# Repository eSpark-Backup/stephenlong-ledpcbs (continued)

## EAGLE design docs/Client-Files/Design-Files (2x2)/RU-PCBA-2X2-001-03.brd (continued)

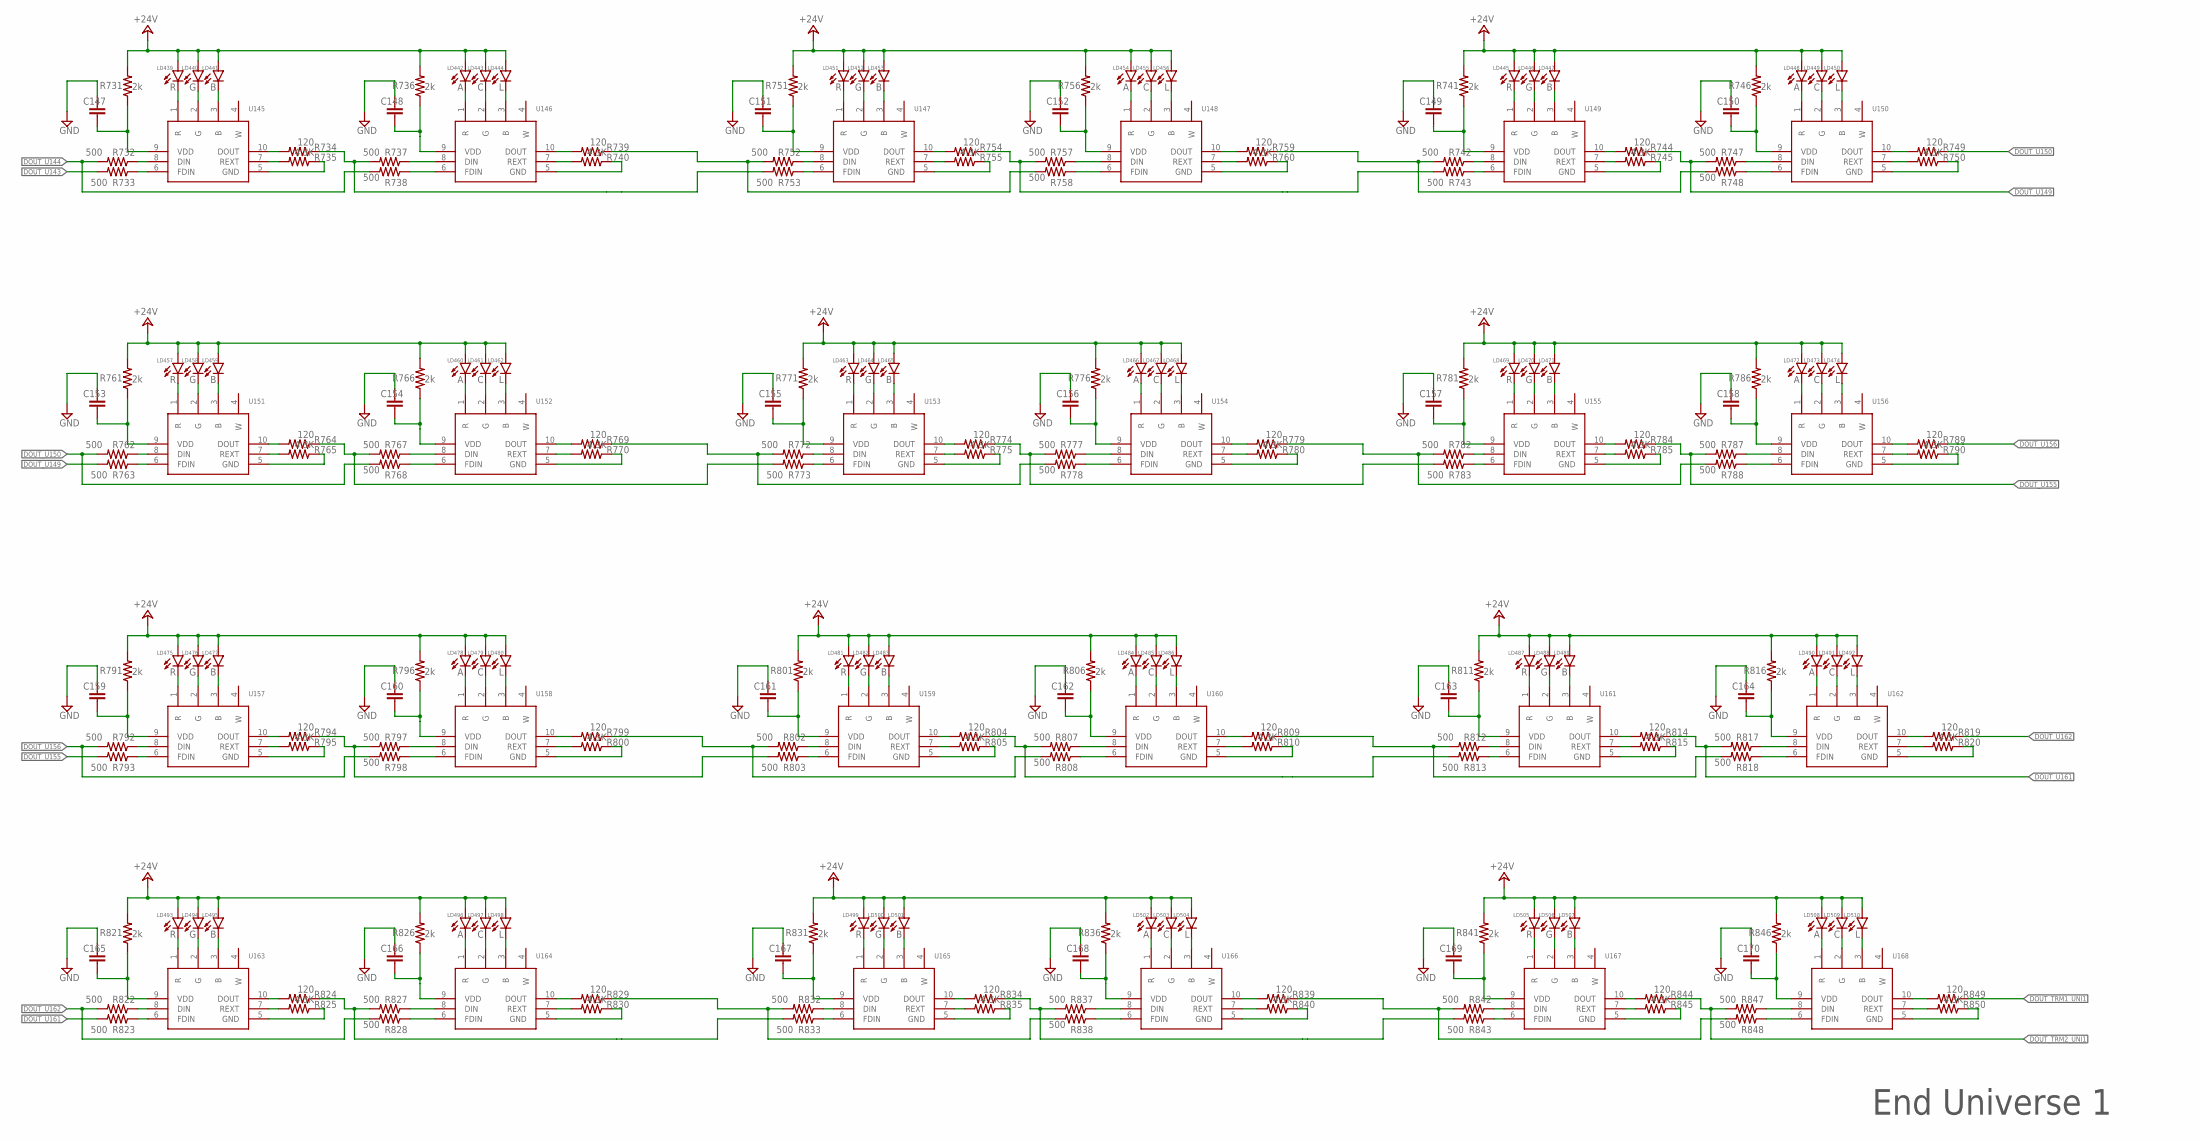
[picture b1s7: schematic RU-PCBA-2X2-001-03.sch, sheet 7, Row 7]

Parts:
C147, C148, C149, C150, C151, C152, C153, C154, C155, C156, C157, C158, C159, C160, C161, C162, C163, C164, C165, C166, C167, C168, C169, C170: C-EUC1206; C1206; MPN C_104
LD439, LD445, LD451, LD457, LD463, LD469, LD475, LD481, LD487, LD493, LD499, LD505: R; 5050LED; MPN R_5050
LD440, LD446, LD452, LD458, LD464, LD470, LD476, LD482, LD488, LD494, LD500, LD506: G; 5050LED; MPN G_5050
LD441, LD447, LD453, LD459, LD465, LD471, LD477, LD483, LD489, LD495, LD501, LD507: B; 5050LED; MPN B_5050
LD442, LD448, LD454, LD460, LD466, LD472, LD478, LD484, LD490, LD496, LD502, LD508: A; 5050LED; MPN A_5050
LD443, LD449, LD455, LD461, LD467, LD473, LD479, LD485, LD491, LD497, LD503, LD509: C; 5050LED; MPN C_5050
LD444, LD450, LD456, LD462, LD468, LD474, LD480, LD486, LD492, LD498, LD504, LD510: L; 5050LED; MPN L_5050
R731, R736, R741, R746, R751, R756, R761, R766, R771, R776, R781, R786, R791, R796, R801, R806, R811, R816, R821, R826, R831, R836, R841, R846: 2k; R1206; MPN R_VDD
R732, R733, R737, R738, R742, R743, R747, R748, R752, R753, R757, R758, R762, R763, R767, R768, R772, R773, R777, R778, R782, R783, R787, R788, R792, R793, R797, R798, R802, R803, R807, R808, R812, R813, R817, R818, R822, R823, R827, R828, R832, R833, R837, R838, R842, R843, R847, R848: 500; R0805; MPN R_500
R734, R739, R744, R749, R754, R759, R764, R769, R774, R779, R784, R789, R794, R799, R804, R809, R814, R819, R824, R829, R834, R839, R844, R849: 120; R0805; MPN R_120
R735, R740, R745, R750, R755, R760, R765, R770, R775, R780, R785, R790, R795, R800, R805, R810, R815, R820, R825, R830, R835, R840, R845, R850: 4.3K; R0805; MPN R_EXT
U145, U146, U147, U148, U149, U150, U151, U152, U153, U154, U155, U156, U157, U158, U159, U160, U161, U162, U163, U164, U165, U166, U167, U168: UCS7604; SOP100P600X175-10N; MPN UCS7604

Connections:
+24V: LD439.A, LD440.A, LD441.A, LD442.A, LD443.A, LD444.A, LD445.A, LD446.A, LD447.A, LD448.A, LD449.A, LD450.A, LD451.A, LD452.A, LD453.A, LD454.A, LD455.A, LD456.A, LD457.A, LD458.A, LD459.A, LD460.A, LD461.A, LD462.A, LD463.A, LD464.A, LD465.A, LD466.A, LD467.A, LD468.A, LD469.A, LD470.A, LD471.A, LD472.A, LD473.A, LD474.A, LD475.A, LD476.A, LD477.A, LD478.A, LD479.A, LD480.A, LD481.A, LD482.A, LD483.A, LD484.A, LD485.A, LD486.A, LD487.A, LD488.A, LD489.A, LD490.A, LD491.A, LD492.A, LD493.A, LD494.A, LD495.A, LD496.A, LD497.A, LD498.A, LD499.A, LD500.A, LD501.A, LD502.A, LD503.A, LD504.A, LD505.A, LD506.A, LD507.A, LD508.A, LD509.A, LD510.A, R731.2, R736.2, R741.2, R746.2, R751.2, R756.2, R761.2, R766.2, R771.2, R776.2, R781.2, R786.2, R791.2, R796.2, R801.2, R806.2, R811.2, R816.2, R821.2, R826.2, R831.2, R836.2, R841.2, R846.2; also elsewhere on the board
DOUT_TRM1_UNI1: R849.1
DOUT_TRM2_UNI1: R844.1, R847.2
DOUT_U143: R733.2; also elsewhere on the board
DOUT_U144: R732.2, R738.2; also elsewhere on the board
DOUT_U149: R744.1, R747.2, R763.2
DOUT_U150: R749.1, R762.2, R768.2
DOUT_U155: R784.1, R787.2, R793.2
DOUT_U156: R789.1, R792.2, R798.2
DOUT_U161: R814.1, R817.2, R823.2
DOUT_U162: R819.1, R822.2, R828.2
GND: C147.2, C148.2, C149.2, C150.2, C151.2, C152.2, C153.2, C154.2, C155.2, C156.2, C157.2, C158.2, C159.2, C160.2, C161.2, C162.2, C163.2, C164.2, C165.2, C166.2, C167.2, C168.2, C169.2, C170.2, R735.1, R740.1, R745.1, R750.1, R755.1, R760.1, R765.1, R770.1, R775.1, R780.1, R785.1, R790.1, R795.1, R800.1, R805.1, R810.1, R815.1, R820.1, R825.1, R830.1, R835.1, R840.1, R845.1, R850.1, U145.5 (GND), U146.5 (GND), U147.5 (GND), U148.5 (GND), U149.5 (GND), U150.5 (GND), U151.5 (GND), U152.5 (GND), U153.5 (GND), U154.5 (GND), U155.5 (GND), U156.5 (GND), U157.5 (GND), U158.5 (GND), U159.5 (GND), U160.5 (GND), U161.5 (GND), U162.5 (GND), U163.5 (GND), U164.5 (GND), U165.5 (GND), U166.5 (GND), U167.5 (GND), U168.5 (GND); also elsewhere on the board
unnamed: C147.1, R731.1, U145.9 (VDD)
unnamed: LD439.K (C), U145.1 (R)
unnamed: LD440.K (C), U145.2 (G)
unnamed: LD441.K (C), U145.3 (B)
unnamed: R732.1, U145.8 (DIN)
unnamed: R733.1, U145.6 (FDIN)
unnamed: R734.2, U145.10 (DOUT)
unnamed: R735.2, U145.7 (REXT)
unnamed: LD442.K (C), U146.1 (R)
unnamed: LD443.K (C), U146.2 (G)
unnamed: LD444.K (C), U146.3 (B)
unnamed: C148.1, R736.1, U146.9 (VDD)
unnamed: R737.1, U146.8 (DIN)
unnamed: R738.1, U146.6 (FDIN)
unnamed: R739.2, U146.10 (DOUT)
unnamed: R740.2, U146.7 (REXT)
unnamed: R739.1, R752.2, R758.2
unnamed: C149.1, R741.1, U149.9 (VDD)
unnamed: LD445.K (C), U149.1 (R)
unnamed: LD446.K (C), U149.2 (G)
unnamed: LD447.K (C), U149.3 (B)
unnamed: R742.1, U149.8 (DIN)
unnamed: R743.1, U149.6 (FDIN)
unnamed: R744.2, U149.10 (DOUT)
unnamed: R745.2, U149.7 (REXT)
unnamed: LD448.K (C), U150.1 (R)
unnamed: LD449.K (C), U150.2 (G)
unnamed: LD450.K (C), U150.3 (B)
unnamed: C150.1, R746.1, U150.9 (VDD)
unnamed: R747.1, U150.8 (DIN)
unnamed: R748.1, U150.6 (FDIN)
unnamed: R743.2, R754.1, R757.2
unnamed: R749.2, U150.10 (DOUT)
unnamed: R750.2, U150.7 (REXT)
unnamed: C151.1, R751.1, U147.9 (VDD)
unnamed: LD451.K (C), U147.1 (R)
unnamed: LD452.K (C), U147.2 (G)
unnamed: LD453.K (C), U147.3 (B)
unnamed: R752.1, U147.8 (DIN)
unnamed: R753.1, U147.6 (FDIN)
unnamed: R754.2, U147.10 (DOUT)
unnamed: R755.2, U147.7 (REXT)
unnamed: LD454.K (C), U148.1 (R)
unnamed: LD455.K (C), U148.2 (G)
unnamed: LD456.K (C), U148.3 (B)
unnamed: C152.1, R756.1, U148.9 (VDD)
unnamed: R757.1, U148.8 (DIN)
unnamed: R758.1, U148.6 (FDIN)
unnamed: R734.1, R737.2, R753.2
unnamed: R759.2, U148.10 (DOUT)
unnamed: R760.2, U148.7 (REXT)
unnamed: R742.2, R748.2, R759.1
unnamed: C153.1, R761.1, U151.9 (VDD)
unnamed: LD457.K (C), U151.1 (R)
unnamed: LD458.K (C), U151.2 (G)
unnamed: LD459.K (C), U151.3 (B)
unnamed: R762.1, U151.8 (DIN)
unnamed: R763.1, U151.6 (FDIN)
unnamed: R764.2, U151.10 (DOUT)
unnamed: R765.2, U151.7 (REXT)
unnamed: LD460.K (C), U152.1 (R)
unnamed: LD461.K (C), U152.2 (G)
unnamed: LD462.K (C), U152.3 (B)
unnamed: C154.1, R766.1, U152.9 (VDD)
unnamed: R767.1, U152.8 (DIN)
unnamed: R768.1, U152.6 (FDIN)
unnamed: R769.2, U152.10 (DOUT)
unnamed: R770.2, U152.7 (REXT)
unnamed: R769.1, R772.2, R778.2
unnamed: C155.1, R771.1, U153.9 (VDD)
unnamed: LD463.K (C), U153.1 (R)
unnamed: LD464.K (C), U153.2 (G)
unnamed: LD465.K (C), U153.3 (B)
unnamed: R772.1, U153.8 (DIN)
unnamed: R773.1, U153.6 (FDIN)
unnamed: R774.2, U153.10 (DOUT)
unnamed: R775.2, U153.7 (REXT)
unnamed: LD466.K (C), U154.1 (R)
unnamed: LD467.K (C), U154.2 (G)
unnamed: LD468.K (C), U154.3 (B)
unnamed: C156.1, R776.1, U154.9 (VDD)
unnamed: R777.1, U154.8 (DIN)
unnamed: R778.1, U154.6 (FDIN)
unnamed: R764.1, R767.2, R773.2
unnamed: R779.2, U154.10 (DOUT)
unnamed: R780.2, U154.7 (REXT)
unnamed: R779.1, R782.2, R788.2
unnamed: C157.1, R781.1, U155.9 (VDD)
unnamed: LD469.K (C), U155.1 (R)
unnamed: LD470.K (C), U155.2 (G)
unnamed: LD471.K (C), U155.3 (B)
unnamed: R782.1, U155.8 (DIN)
unnamed: R783.1, U155.6 (FDIN)
unnamed: R784.2, U155.10 (DOUT)
unnamed: R785.2, U155.7 (REXT)
unnamed: LD472.K (C), U156.1 (R)
unnamed: LD473.K (C), U156.2 (G)
unnamed: LD474.K (C), U156.3 (B)
unnamed: C158.1, R786.1, U156.9 (VDD)
unnamed: R787.1, U156.8 (DIN)
unnamed: R788.1, U156.6 (FDIN)
unnamed: R774.1, R777.2, R783.2
unnamed: R789.2, U156.10 (DOUT)
unnamed: R790.2, U156.7 (REXT)
unnamed: C159.1, R791.1, U157.9 (VDD)
unnamed: LD475.K (C), U157.1 (R)
unnamed: LD476.K (C), U157.2 (G)
unnamed: LD477.K (C), U157.3 (B)
unnamed: R792.1, U157.8 (DIN)
unnamed: R793.1, U157.6 (FDIN)
unnamed: R794.2, U157.10 (DOUT)
unnamed: R795.2, U157.7 (REXT)
unnamed: LD478.K (C), U158.1 (R)
unnamed: LD479.K (C), U158.2 (G)
unnamed: LD480.K (C), U158.3 (B)
unnamed: C160.1, R796.1, U158.9 (VDD)
unnamed: R797.1, U158.8 (DIN)
unnamed: R798.1, U158.6 (FDIN)
unnamed: R799.2, U158.10 (DOUT)
unnamed: R800.2, U158.7 (REXT)
unnamed: R799.1, R802.2, R808.2
unnamed: C161.1, R801.1, U159.9 (VDD)
unnamed: LD481.K (C), U159.1 (R)
unnamed: LD482.K (C), U159.2 (G)
unnamed: LD483.K (C), U159.3 (B)
unnamed: R802.1, U159.8 (DIN)
unnamed: R803.1, U159.6 (FDIN)
unnamed: R804.2, U159.10 (DOUT)
unnamed: R805.2, U159.7 (REXT)
unnamed: LD484.K (C), U160.1 (R)
unnamed: LD485.K (C), U160.2 (G)
unnamed: LD486.K (C), U160.3 (B)
unnamed: C162.1, R806.1, U160.9 (VDD)
unnamed: R807.1, U160.8 (DIN)
unnamed: R808.1, U160.6 (FDIN)
unnamed: R794.1, R797.2, R803.2
unnamed: R809.2, U160.10 (DOUT)
unnamed: R810.2, U160.7 (REXT)
unnamed: R809.1, R812.2, R818.2
unnamed: C163.1, R811.1, U161.9 (VDD)
unnamed: LD487.K (C), U161.1 (R)
unnamed: LD488.K (C), U161.2 (G)
unnamed: LD489.K (C), U161.3 (B)
unnamed: R812.1, U161.8 (DIN)
unnamed: R813.1, U161.6 (FDIN)
unnamed: R814.2, U161.10 (DOUT)
unnamed: R815.2, U161.7 (REXT)
unnamed: LD490.K (C), U162.1 (R)
unnamed: LD491.K (C), U162.2 (G)
unnamed: LD492.K (C), U162.3 (B)
unnamed: C164.1, R816.1, U162.9 (VDD)
unnamed: R817.1, U162.8 (DIN)
unnamed: R818.1, U162.6 (FDIN)
unnamed: R804.1, R807.2, R813.2
unnamed: R819.2, U162.10 (DOUT)
unnamed: R820.2, U162.7 (REXT)
unnamed: C165.1, R821.1, U163.9 (VDD)
unnamed: LD493.K (C), U163.1 (R)
unnamed: LD494.K (C), U163.2 (G)
unnamed: LD495.K (C), U163.3 (B)
unnamed: R822.1, U163.8 (DIN)
unnamed: R823.1, U163.6 (FDIN)
unnamed: R824.2, U163.10 (DOUT)
unnamed: R825.2, U163.7 (REXT)
unnamed: LD496.K (C), U164.1 (R)
unnamed: LD497.K (C), U164.2 (G)
unnamed: LD498.K (C), U164.3 (B)
unnamed: C166.1, R826.1, U164.9 (VDD)
unnamed: R827.1, U164.8 (DIN)
unnamed: R828.1, U164.6 (FDIN)
unnamed: R829.2, U164.10 (DOUT)
unnamed: R830.2, U164.7 (REXT)
unnamed: R829.1, R832.2, R838.2
unnamed: C167.1, R831.1, U165.9 (VDD)
unnamed: LD499.K (C), U165.1 (R)
unnamed: LD500.K (C), U165.2 (G)
unnamed: LD501.K (C), U165.3 (B)
unnamed: R832.1, U165.8 (DIN)
unnamed: R833.1, U165.6 (FDIN)
unnamed: R834.2, U165.10 (DOUT)
unnamed: R835.2, U165.7 (REXT)
unnamed: LD502.K (C), U166.1 (R)
unnamed: LD503.K (C), U166.2 (G)
unnamed: LD504.K (C), U166.3 (B)
unnamed: C168.1, R836.1, U166.9 (VDD)
unnamed: R837.1, U166.8 (DIN)
unnamed: R834.1, R837.2, R843.2
unnamed: R838.1, U166.6 (FDIN)
unnamed: R824.1, R827.2, R833.2
unnamed: R839.2, U166.10 (DOUT)
unnamed: R840.2, U166.7 (REXT)
unnamed: R839.1, R842.2, R848.2
unnamed: C169.1, R841.1, U167.9 (VDD)
unnamed: LD505.K (C), U167.1 (R)
unnamed: LD506.K (C), U167.2 (G)
unnamed: LD507.K (C), U167.3 (B)
unnamed: R842.1, U167.8 (DIN)
unnamed: R843.1, U167.6 (FDIN)
unnamed: R844.2, U167.10 (DOUT)
unnamed: R845.2, U167.7 (REXT)
unnamed: LD508.K (C), U168.1 (R)
unnamed: LD509.K (C), U168.2 (G)
unnamed: LD510.K (C), U168.3 (B)
unnamed: C170.1, R846.1, U168.9 (VDD)
unnamed: R847.1, U168.8 (DIN)
unnamed: R848.1, U168.6 (FDIN)
unnamed: R849.2, U168.10 (DOUT)
unnamed: R850.2, U168.7 (REXT)

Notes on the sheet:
End Universe 1

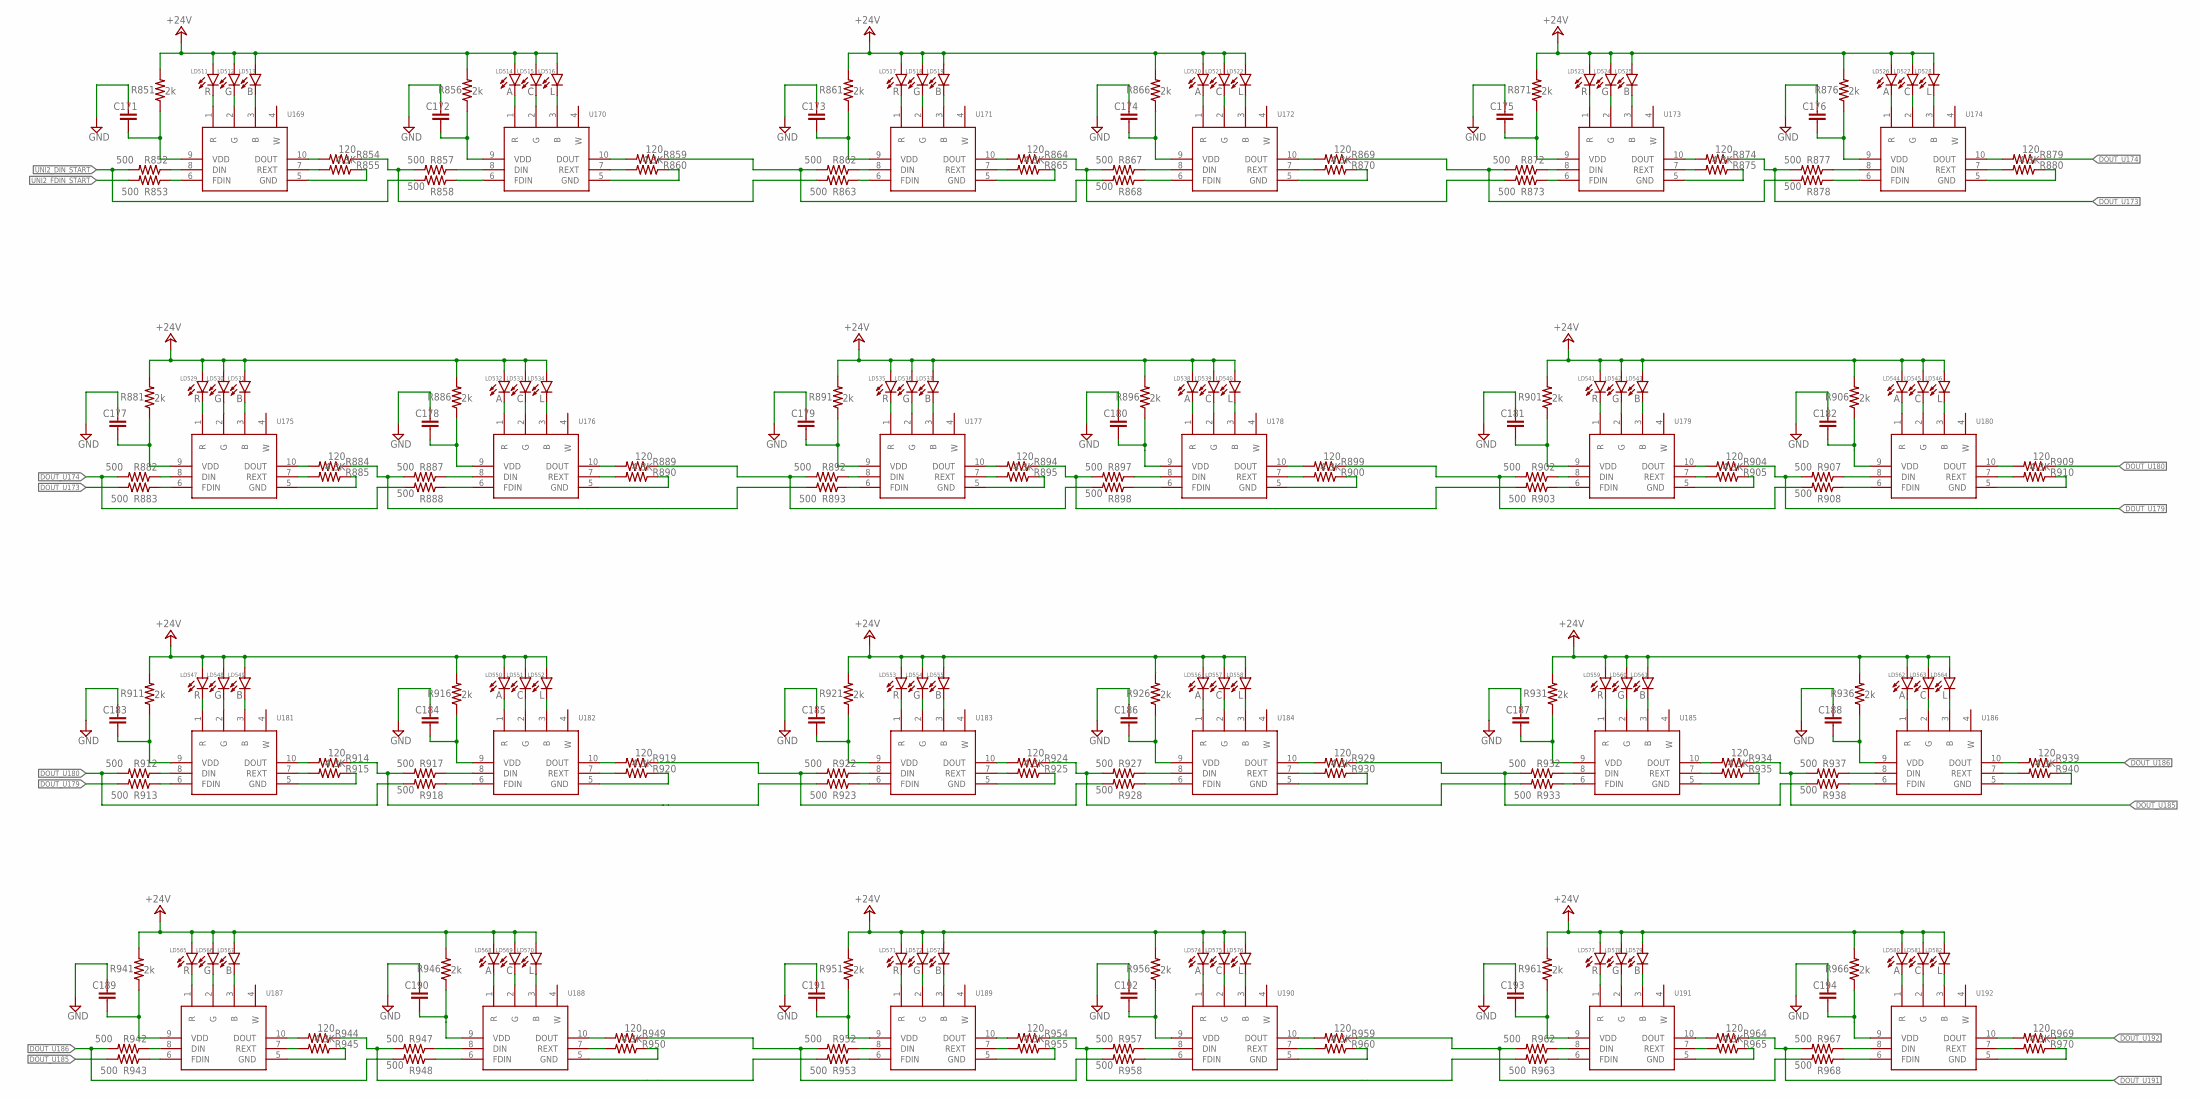
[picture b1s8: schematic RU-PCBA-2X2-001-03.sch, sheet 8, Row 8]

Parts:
C171, C172, C173, C174, C175, C176, C177, C178, C179, C180, C181, C182, C183, C184, C185, C186, C187, C188, C189, C190, C191, C192, C193, C194: C-EUC1206; C1206; MPN C_104
LD511, LD517, LD523, LD529, LD535, LD541, LD547, LD553, LD559, LD565, LD571, LD577: R; 5050LED; MPN R_5050
LD512, LD518, LD524, LD530, LD536, LD542, LD548, LD554, LD560, LD566, LD572, LD578: G; 5050LED; MPN G_5050
LD513, LD519, LD525, LD531, LD537, LD543, LD549, LD555, LD561, LD567, LD573, LD579: B; 5050LED; MPN B_5050
LD514, LD520, LD526, LD532, LD538, LD544, LD550, LD556, LD562, LD568, LD574, LD580: A; 5050LED; MPN A_5050
LD515, LD521, LD527, LD533, LD539, LD545, LD551, LD557, LD563, LD569, LD575, LD581: C; 5050LED; MPN C_5050
LD516, LD522, LD528, LD534, LD540, LD546, LD552, LD558, LD564, LD570, LD576, LD582: L; 5050LED; MPN L_5050
R851, R856, R861, R866, R871, R876, R881, R886, R891, R896, R901, R906, R911, R916, R921, R926, R931, R936, R941, R946, R951, R956, R961, R966: 2k; R1206; MPN R_VDD
R852, R853, R857, R858, R862, R863, R867, R868, R872, R873, R877, R878, R882, R883, R887, R888, R892, R893, R897, R898, R902, R903, R907, R908, R912, R913, R917, R918, R922, R923, R927, R928, R932, R933, R937, R938, R942, R943, R947, R948, R952, R953, R957, R958, R962, R963, R967, R968: 500; R0805; MPN R_500
R854, R859, R864, R869, R874, R879, R884, R889, R894, R899, R904, R909, R914, R919, R924, R929, R934, R939, R944, R949, R954, R959, R964, R969: 120; R0805; MPN R_120
R855, R860, R865, R870, R875, R880, R885, R890, R895, R900, R905, R910, R915, R920, R925, R930, R935, R940, R945, R950, R955, R960, R965, R970: 4.3K; R0805; MPN R_EXT
U169, U170, U171, U172, U173, U174, U175, U176, U177, U178, U179, U180, U181, U182, U183, U184, U185, U186, U187, U188, U189, U190, U191, U192: UCS7604; SOP100P600X175-10N; MPN UCS7604

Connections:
+24V: LD511.A, LD512.A, LD513.A, LD514.A, LD515.A, LD516.A, LD517.A, LD518.A, LD519.A, LD520.A, LD521.A, LD522.A, LD523.A, LD524.A, LD525.A, LD526.A, LD527.A, LD528.A, LD529.A, LD530.A, LD531.A, LD532.A, LD533.A, LD534.A, LD535.A, LD536.A, LD537.A, LD538.A, LD539.A, LD540.A, LD541.A, LD542.A, LD543.A, LD544.A, LD545.A, LD546.A, LD547.A, LD548.A, LD549.A, LD550.A, LD551.A, LD552.A, LD553.A, LD554.A, LD555.A, LD556.A, LD557.A, LD558.A, LD559.A, LD560.A, LD561.A, LD562.A, LD563.A, LD564.A, LD565.A, LD566.A, LD567.A, LD568.A, LD569.A, LD570.A, LD571.A, LD572.A, LD573.A, LD574.A, LD575.A, LD576.A, LD577.A, LD578.A, LD579.A, LD580.A, LD581.A, LD582.A, R851.2, R856.2, R861.2, R866.2, R871.2, R876.2, R881.2, R886.2, R891.2, R896.2, R901.2, R906.2, R911.2, R916.2, R921.2, R926.2, R931.2, R936.2, R941.2, R946.2, R951.2, R956.2, R961.2, R966.2; also elsewhere on the board
DOUT_U173: R874.1, R877.2, R883.2
DOUT_U174: R879.1, R882.2, R888.2
DOUT_U179: R904.1, R907.2, R913.2
DOUT_U180: R909.1, R912.2, R918.2
DOUT_U185: R934.1, R937.2, R943.2
DOUT_U186: R939.1, R942.2, R948.2
DOUT_U191: R964.1, R967.2; also elsewhere on the board
DOUT_U192: R969.1; also elsewhere on the board
GND: C171.2, C172.2, C173.2, C174.2, C175.2, C176.2, C177.2, C178.2, C179.2, C180.2, C181.2, C182.2, C183.2, C184.2, C185.2, C186.2, C187.2, C188.2, C189.2, C190.2, C191.2, C192.2, C193.2, C194.2, R855.1, R860.1, R865.1, R870.1, R875.1, R880.1, R885.1, R890.1, R895.1, R900.1, R905.1, R910.1, R915.1, R920.1, R925.1, R930.1, R935.1, R940.1, R945.1, R950.1, R955.1, R960.1, R965.1, R970.1, U169.5 (GND), U170.5 (GND), U171.5 (GND), U172.5 (GND), U173.5 (GND), U174.5 (GND), U175.5 (GND), U176.5 (GND), U177.5 (GND), U178.5 (GND), U179.5 (GND), U180.5 (GND), U181.5 (GND), U182.5 (GND), U183.5 (GND), U184.5 (GND), U185.5 (GND), U186.5 (GND), U187.5 (GND), U188.5 (GND), U189.5 (GND), U190.5 (GND), U191.5 (GND), U192.5 (GND); also elsewhere on the board
unnamed: C171.1, R851.1, U169.9 (VDD)
unnamed: LD511.K (C), U169.1 (R)
unnamed: LD512.K (C), U169.2 (G)
unnamed: LD513.K (C), U169.3 (B)
unnamed: R852.1, U169.8 (DIN)
unnamed: R853.1, U169.6 (FDIN)
unnamed: R854.2, U169.10 (DOUT)
unnamed: R855.2, U169.7 (REXT)
unnamed: LD514.K (C), U170.1 (R)
unnamed: LD515.K (C), U170.2 (G)
unnamed: LD516.K (C), U170.3 (B)
unnamed: C172.1, R856.1, U170.9 (VDD)
unnamed: R857.1, U170.8 (DIN)
unnamed: R858.1, U170.6 (FDIN)
unnamed: R859.2, U170.10 (DOUT)
unnamed: R860.2, U170.7 (REXT)
unnamed: R859.1, R862.2, R868.2
unnamed: C173.1, R861.1, U171.9 (VDD)
unnamed: LD517.K (C), U171.1 (R)
unnamed: LD518.K (C), U171.2 (G)
unnamed: LD519.K (C), U171.3 (B)
unnamed: R862.1, U171.8 (DIN)
unnamed: R863.1, U171.6 (FDIN)
unnamed: R864.2, U171.10 (DOUT)
unnamed: R865.2, U171.7 (REXT)
unnamed: LD520.K (C), U172.1 (R)
unnamed: LD521.K (C), U172.2 (G)
unnamed: LD522.K (C), U172.3 (B)
unnamed: C174.1, R866.1, U172.9 (VDD)
unnamed: R867.1, U172.8 (DIN)
unnamed: R868.1, U172.6 (FDIN)
unnamed: R854.1, R857.2, R863.2
unnamed: R869.2, U172.10 (DOUT)
unnamed: R870.2, U172.7 (REXT)
unnamed: R869.1, R872.2, R878.2
unnamed: C175.1, R871.1, U173.9 (VDD)
unnamed: LD523.K (C), U173.1 (R)
unnamed: LD524.K (C), U173.2 (G)
unnamed: LD525.K (C), U173.3 (B)
unnamed: R872.1, U173.8 (DIN)
unnamed: R873.1, U173.6 (FDIN)
unnamed: R874.2, U173.10 (DOUT)
unnamed: R875.2, U173.7 (REXT)
unnamed: LD526.K (C), U174.1 (R)
unnamed: LD527.K (C), U174.2 (G)
unnamed: LD528.K (C), U174.3 (B)
unnamed: C176.1, R876.1, U174.9 (VDD)
unnamed: R877.1, U174.8 (DIN)
unnamed: R878.1, U174.6 (FDIN)
unnamed: R864.1, R867.2, R873.2
unnamed: R879.2, U174.10 (DOUT)
unnamed: R880.2, U174.7 (REXT)
unnamed: C177.1, R881.1, U175.9 (VDD)
unnamed: LD529.K (C), U175.1 (R)
unnamed: LD530.K (C), U175.2 (G)
unnamed: LD531.K (C), U175.3 (B)
unnamed: R882.1, U175.8 (DIN)
unnamed: R883.1, U175.6 (FDIN)
unnamed: R884.2, U175.10 (DOUT)
unnamed: R885.2, U175.7 (REXT)
unnamed: LD532.K (C), U176.1 (R)
unnamed: LD533.K (C), U176.2 (G)
unnamed: LD534.K (C), U176.3 (B)
unnamed: C178.1, R886.1, U176.9 (VDD)
unnamed: R887.1, U176.8 (DIN)
unnamed: R888.1, U176.6 (FDIN)
unnamed: R889.2, U176.10 (DOUT)
unnamed: R890.2, U176.7 (REXT)
unnamed: R889.1, R892.2, R898.2
unnamed: C179.1, R891.1, U177.9 (VDD)
unnamed: LD535.K (C), U177.1 (R)
unnamed: LD536.K (C), U177.2 (G)
unnamed: LD537.K (C), U177.3 (B)
unnamed: R892.1, U177.8 (DIN)
unnamed: R893.1, U177.6 (FDIN)
unnamed: R894.2, U177.10 (DOUT)
unnamed: R895.2, U177.7 (REXT)
unnamed: LD538.K (C), U178.1 (R)
unnamed: LD539.K (C), U178.2 (G)
unnamed: LD540.K (C), U178.3 (B)
unnamed: C180.1, R896.1, U178.9 (VDD)
unnamed: R897.1, U178.8 (DIN)
unnamed: R898.1, U178.6 (FDIN)
unnamed: R884.1, R887.2, R893.2
unnamed: R899.2, U178.10 (DOUT)
unnamed: R900.2, U178.7 (REXT)
unnamed: R899.1, R902.2, R908.2
unnamed: C181.1, R901.1, U179.9 (VDD)
unnamed: LD541.K (C), U179.1 (R)
unnamed: LD542.K (C), U179.2 (G)
unnamed: LD543.K (C), U179.3 (B)
unnamed: R902.1, U179.8 (DIN)
unnamed: R903.1, U179.6 (FDIN)
unnamed: R904.2, U179.10 (DOUT)
unnamed: R905.2, U179.7 (REXT)
unnamed: LD544.K (C), U180.1 (R)
unnamed: LD545.K (C), U180.2 (G)
unnamed: LD546.K (C), U180.3 (B)
unnamed: C182.1, R906.1, U180.9 (VDD)
unnamed: R907.1, U180.8 (DIN)
unnamed: R908.1, U180.6 (FDIN)
unnamed: R894.1, R897.2, R903.2
unnamed: R909.2, U180.10 (DOUT)
unnamed: R910.2, U180.7 (REXT)
unnamed: C183.1, R911.1, U181.9 (VDD)
unnamed: LD547.K (C), U181.1 (R)
unnamed: LD548.K (C), U181.2 (G)
unnamed: LD549.K (C), U181.3 (B)
unnamed: R912.1, U181.8 (DIN)
unnamed: R913.1, U181.6 (FDIN)
unnamed: R914.2, U181.10 (DOUT)
unnamed: R915.2, U181.7 (REXT)
unnamed: LD550.K (C), U182.1 (R)
unnamed: LD551.K (C), U182.2 (G)
unnamed: LD552.K (C), U182.3 (B)
unnamed: C184.1, R916.1, U182.9 (VDD)
unnamed: R917.1, U182.8 (DIN)
unnamed: R918.1, U182.6 (FDIN)
unnamed: R919.2, U182.10 (DOUT)
unnamed: R920.2, U182.7 (REXT)
unnamed: R919.1, R922.2, R928.2
unnamed: C185.1, R921.1, U183.9 (VDD)
unnamed: LD553.K (C), U183.1 (R)
unnamed: LD554.K (C), U183.2 (G)
unnamed: LD555.K (C), U183.3 (B)
unnamed: R922.1, U183.8 (DIN)
unnamed: R923.1, U183.6 (FDIN)
unnamed: R924.2, U183.10 (DOUT)
unnamed: R925.2, U183.7 (REXT)
unnamed: LD556.K (C), U184.1 (R)
unnamed: LD557.K (C), U184.2 (G)
unnamed: LD558.K (C), U184.3 (B)
unnamed: C186.1, R926.1, U184.9 (VDD)
unnamed: R927.1, U184.8 (DIN)
unnamed: R928.1, U184.6 (FDIN)
unnamed: R914.1, R917.2, R923.2
unnamed: R929.2, U184.10 (DOUT)
unnamed: R930.2, U184.7 (REXT)
unnamed: R929.1, R932.2, R938.2
unnamed: C187.1, R931.1, U185.9 (VDD)
unnamed: LD559.K (C), U185.1 (R)
unnamed: LD560.K (C), U185.2 (G)
unnamed: LD561.K (C), U185.3 (B)
unnamed: R932.1, U185.8 (DIN)
unnamed: R933.1, U185.6 (FDIN)
unnamed: R934.2, U185.10 (DOUT)
unnamed: R935.2, U185.7 (REXT)
unnamed: LD562.K (C), U186.1 (R)
unnamed: LD563.K (C), U186.2 (G)
unnamed: LD564.K (C), U186.3 (B)
unnamed: C188.1, R936.1, U186.9 (VDD)
unnamed: R937.1, U186.8 (DIN)
unnamed: R938.1, U186.6 (FDIN)
unnamed: R924.1, R927.2, R933.2
unnamed: R939.2, U186.10 (DOUT)
unnamed: R940.2, U186.7 (REXT)
unnamed: C189.1, R941.1, U187.9 (VDD)
unnamed: LD565.K (C), U187.1 (R)
unnamed: LD566.K (C), U187.2 (G)
unnamed: LD567.K (C), U187.3 (B)
unnamed: R942.1, U187.8 (DIN)
unnamed: R943.1, U187.6 (FDIN)
unnamed: R944.2, U187.10 (DOUT)
unnamed: R945.2, U187.7 (REXT)
unnamed: LD568.K (C), U188.1 (R)
unnamed: LD569.K (C), U188.2 (G)
unnamed: LD570.K (C), U188.3 (B)
unnamed: C190.1, R946.1, U188.9 (VDD)
unnamed: R947.1, U188.8 (DIN)
unnamed: R948.1, U188.6 (FDIN)
unnamed: R949.2, U188.10 (DOUT)
unnamed: R950.2, U188.7 (REXT)
unnamed: R949.1, R952.2, R958.2
unnamed: C191.1, R951.1, U189.9 (VDD)
unnamed: LD571.K (C), U189.1 (R)
unnamed: LD572.K (C), U189.2 (G)
unnamed: LD573.K (C), U189.3 (B)
unnamed: R952.1, U189.8 (DIN)
unnamed: R953.1, U189.6 (FDIN)
unnamed: R954.2, U189.10 (DOUT)
unnamed: R955.2, U189.7 (REXT)
unnamed: LD574.K (C), U190.1 (R)
unnamed: LD575.K (C), U190.2 (G)
unnamed: LD576.K (C), U190.3 (B)
unnamed: C192.1, R956.1, U190.9 (VDD)
unnamed: R957.1, U190.8 (DIN)
unnamed: R958.1, U190.6 (FDIN)
unnamed: R944.1, R947.2, R953.2
unnamed: R959.2, U190.10 (DOUT)
unnamed: R960.2, U190.7 (REXT)
unnamed: R959.1, R962.2, R968.2
unnamed: C193.1, R961.1, U191.9 (VDD)
unnamed: LD577.K (C), U191.1 (R)
unnamed: LD578.K (C), U191.2 (G)
unnamed: LD579.K (C), U191.3 (B)
unnamed: R962.1, U191.8 (DIN)
unnamed: R963.1, U191.6 (FDIN)
unnamed: R964.2, U191.10 (DOUT)
unnamed: R965.2, U191.7 (REXT)
unnamed: LD580.K (C), U192.1 (R)
unnamed: LD581.K (C), U192.2 (G)
unnamed: LD582.K (C), U192.3 (B)
unnamed: C194.1, R966.1, U192.9 (VDD)
unnamed: R967.1, U192.8 (DIN)
unnamed: R968.1, U192.6 (FDIN)
unnamed: R954.1, R957.2, R963.2
unnamed: R969.2, U192.10 (DOUT)
unnamed: R970.2, U192.7 (REXT)
UNI2_DIN_START: R852.2, R858.2; also elsewhere on the board
UNI2_FDIN_START: R853.2
